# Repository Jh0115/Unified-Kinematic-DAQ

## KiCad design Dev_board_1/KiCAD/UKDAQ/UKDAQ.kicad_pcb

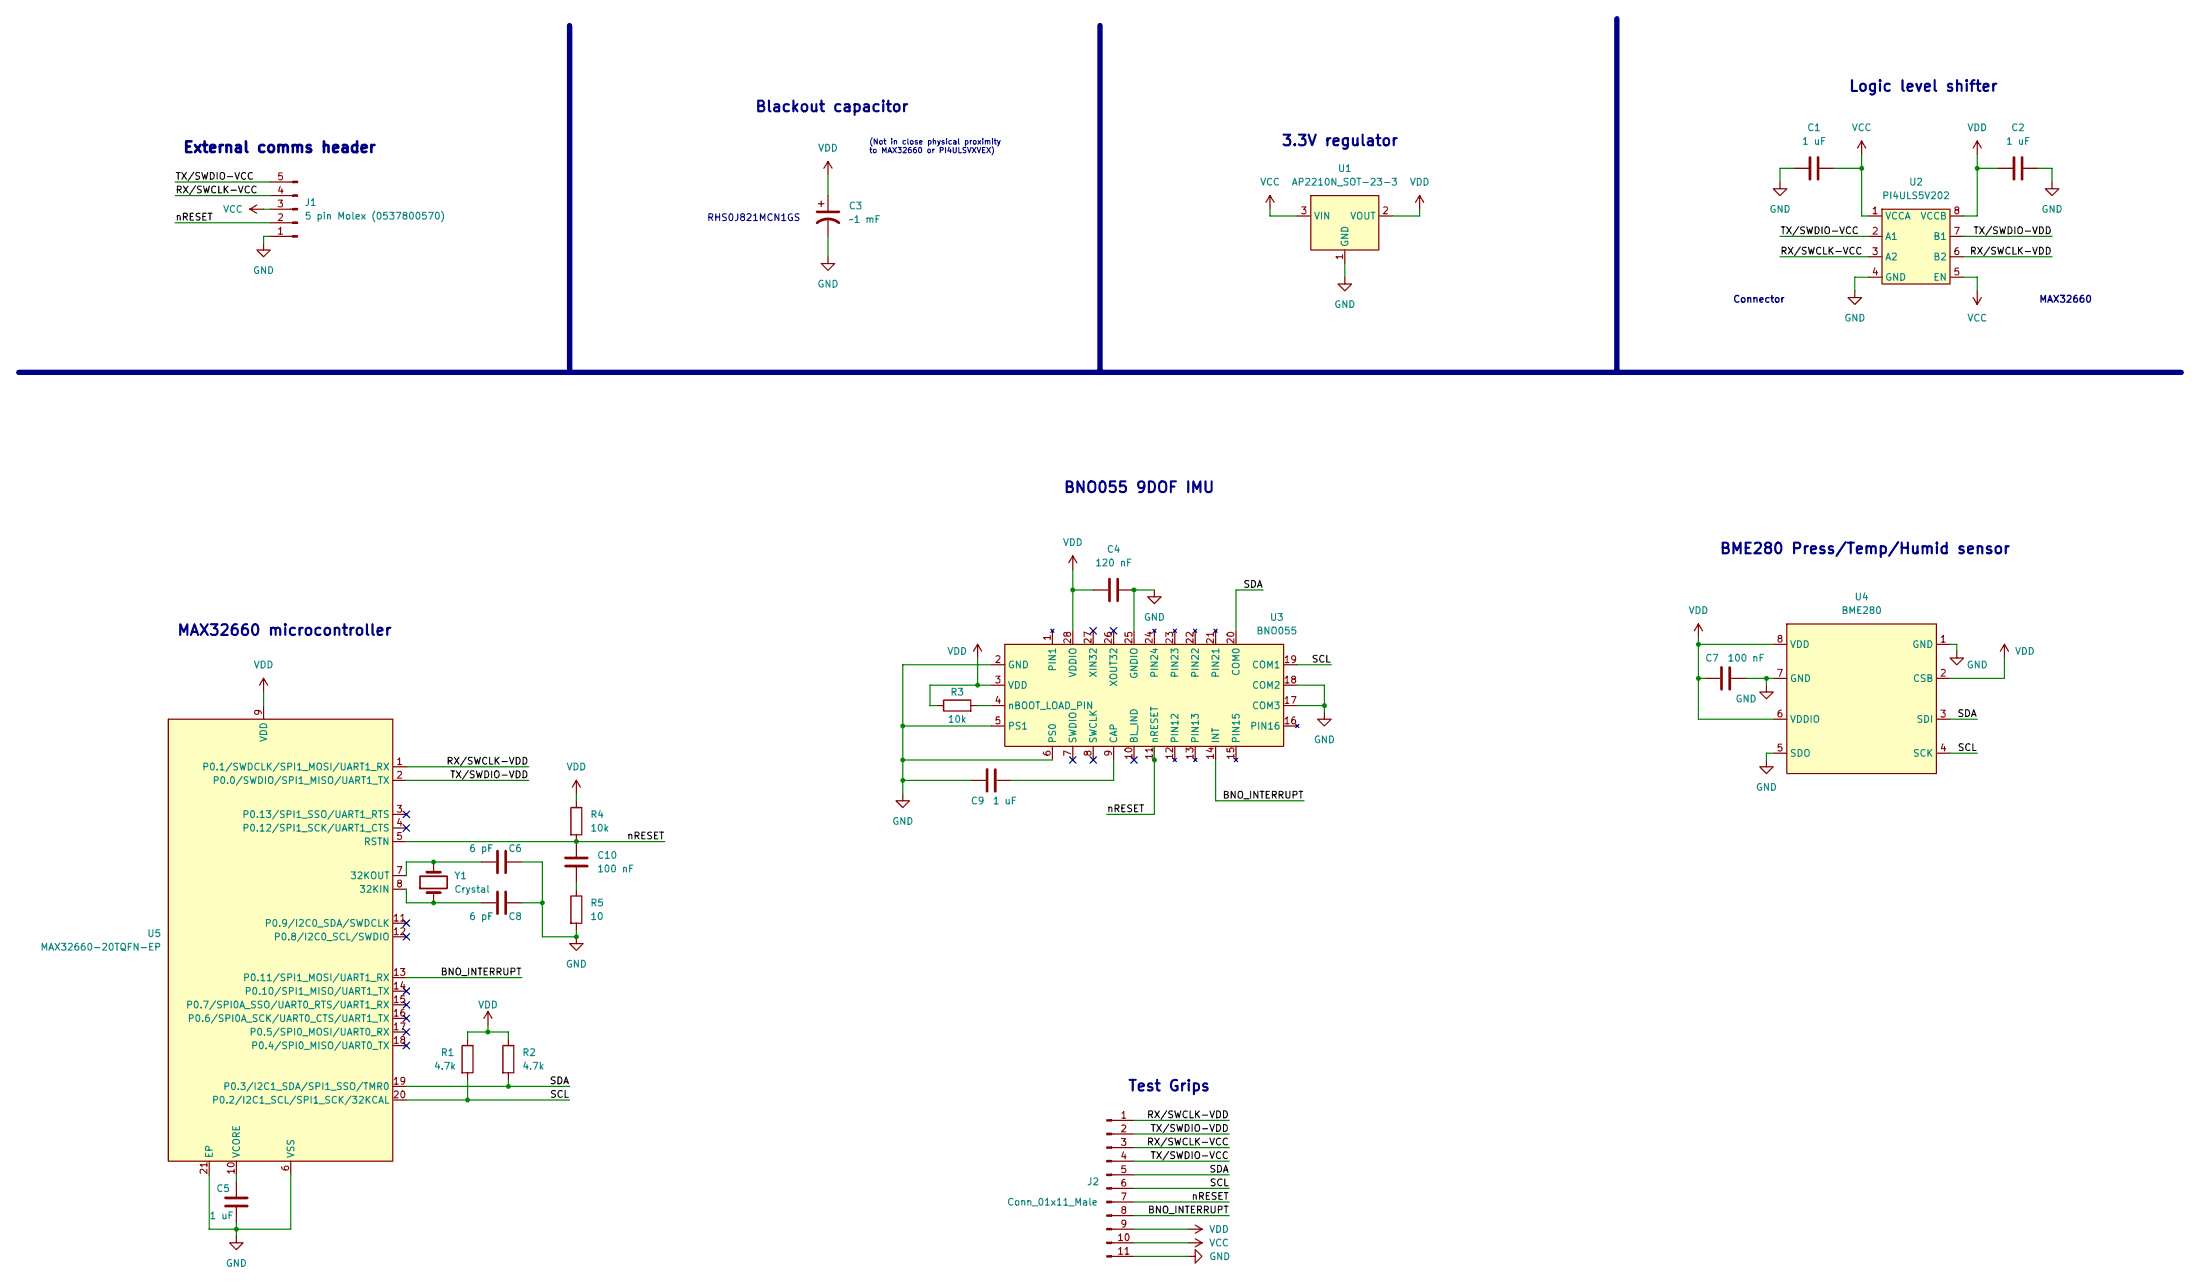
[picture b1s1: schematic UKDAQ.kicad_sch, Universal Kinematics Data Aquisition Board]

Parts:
C1, C2, C5, C9: 1 uF; C_0603_1608Metric
C3: ~1 mF; Can Capacitor - 493-3773-1-ND
C4: 120 nF; C_0603_1608Metric
C6, C8: 6 pF; C_0603_1608Metric
C7, C10: 100 nF; C_0603_1608Metric
J1: 5 pin Molex (0537800570); PinHeader_1x05_P2.54mm_Vertical
J2: Conn_01x11_Male; PinHeader_1x11_P2.54mm_Vertical
R1, R2: 4.7k; R_0402_1005Metric
R3, R4: 10k; R_0402_1005Metric
R5: 10; R_0402_1005Metric
U1: AP2210N_SOT-23-3; SOT-23
U2: PI4ULS5V202; MSOP-8
U3: BNO055; LGA28R50P4X10_380X520X100
U4: BME280
U5: MAX32660-20TQFN-EP; 21-0139V_T2044&plus_5_MXM
Y1: Crystal; Crystal_SMD_3215-2Pin_3.2x1.5mm

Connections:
/BNO_INTERRUPT: J2.8, U3.14 (INT), U5.13 (P0.11/SPI1_MOSI/UART1_RX)
/RX/SWCLK-VCC: J1.4, J2.3, U2.3 (A2)
/RX/SWCLK-VDD: J2.1, U2.6 (B2), U5.1 (P0.1/SWDCLK/SPI1_MOSI/UART1_RX)
/SCL: J2.6, R1.2, U3.19 (COM1), U4.4 (SCK), U5.20 (P0.2/I2C1_SCL/SPI1_SCK/32KCAL)
/SDA: J2.5, R2.2, U3.20 (COM0), U4.3 (SDI), U5.19 (P0.3/I2C1_SDA/SPI1_SSO/TMR0)
/TX/SWDIO-VCC: J1.5, J2.4, U2.2 (A1)
/TX/SWDIO-VDD: J2.2, U2.7 (B1), U5.2 (P0.0/SWDIO/SPI1_MISO/UART1_TX)
/nRESET: C10.1, J1.2, J2.7, R4.2, U3.11 (nRESET), U5.5 (RSTN)
GND: C1.1, C2.2, C3.2, C4.2, C5.2, C6.2, C7.2, C8.2, C9.1, J1.1, J2.11, R5.2, U1.1 (GND), U2.4 (GND), U3.2 (GND), U3.5 (PS1), U3.6 (PS0), U3.17 (COM3), U3.18 (COM2), U3.25 (GNDIO), U4.1 (GND), U4.5 (SDO), U4.7 (GND), U5.6 (VSS), U5.21 (EP)
unnamed: C5.1, U5.10 (VCORE)
unnamed: C6.1, U5.7 (32KOUT), Y1.2
unnamed: C8.1, U5.8 (32KIN), Y1.1
unnamed: C9.2, U3.9 (CAP)
unnamed: C10.2, R5.1
unnamed: R3.2, U3.4 (nBOOT_LOAD_PIN)
VCC: C1.2, J1.3, J2.10, U1.3 (VIN), U2.1 (VCCA), U2.5 (EN)
VDD: C2.1, C3.1, C4.1, C7.1, J2.9, R1.1, R2.1, R3.1, R4.1, U1.2 (VOUT), U2.8 (VCCB), U3.3 (VDD), U3.28 (VDDIO), U4.2 (CSB), U4.6 (VDDIO), U4.8 (VDD), U5.9 (VDD)

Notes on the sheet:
(Not in close physical proximity to MAX32660 or PI4ULSVXVEX)
MAX32660
Connector
BME280 Press/Temp/Humid sensor
External comms header
MAX32660 microcontroller
RHS0J821MCN1GS
Logic level shifter
3.3V regulator
Test Grips
Blackout capacitor
BNO055 9DOF IMU

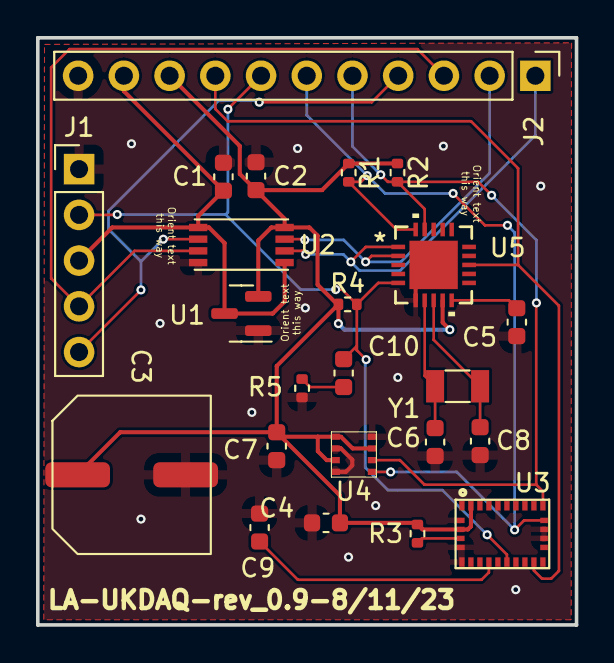
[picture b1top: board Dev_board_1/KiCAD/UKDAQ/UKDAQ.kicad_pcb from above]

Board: 2 copper layers, 29.9 x 32.6 mm, 23 parts (0 on the bottom side), 17 nets.

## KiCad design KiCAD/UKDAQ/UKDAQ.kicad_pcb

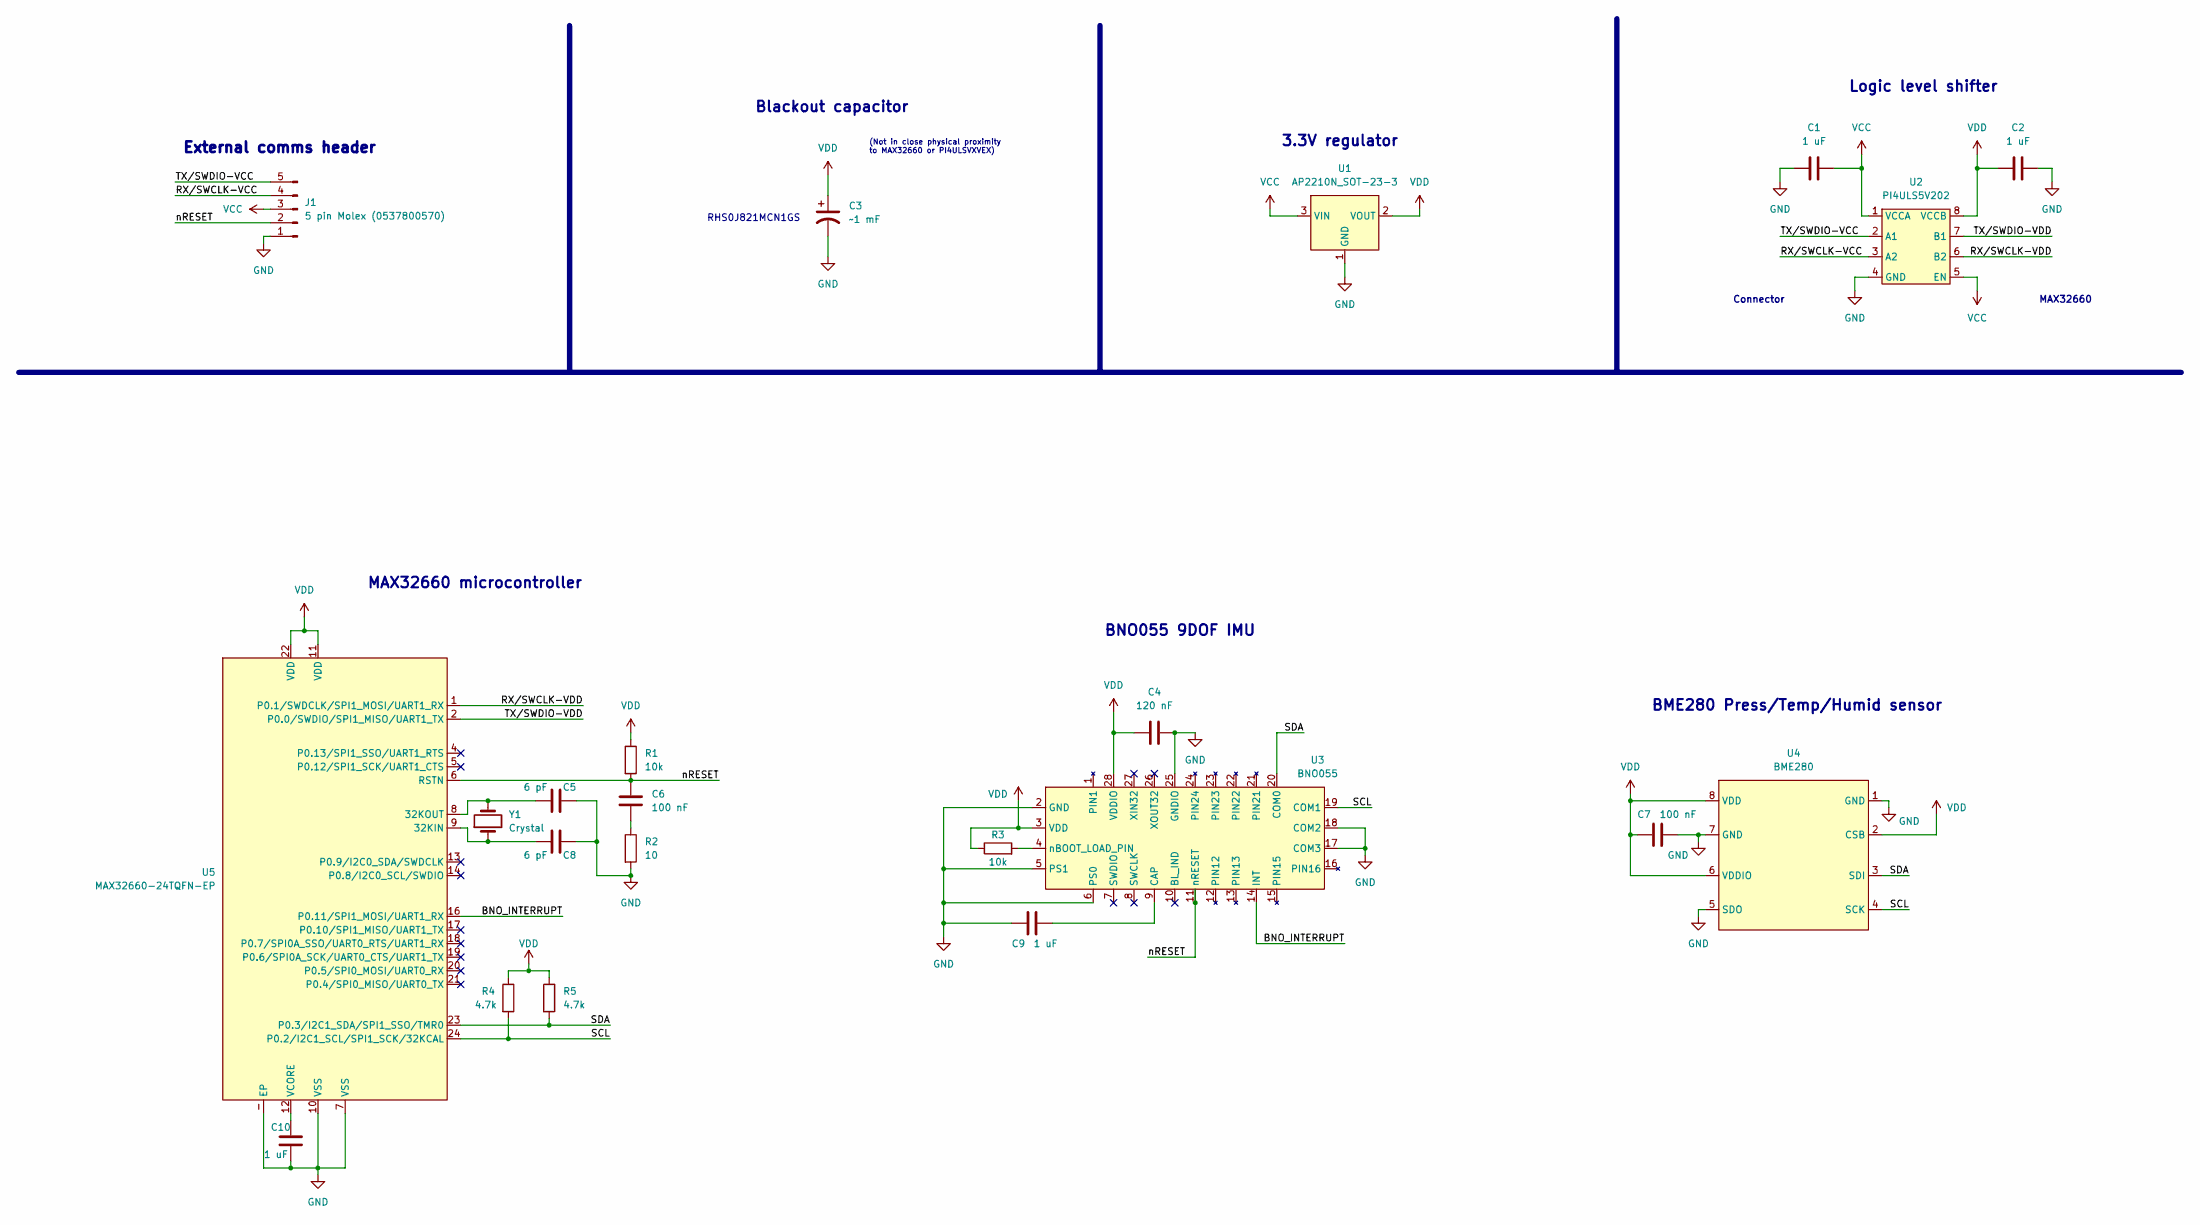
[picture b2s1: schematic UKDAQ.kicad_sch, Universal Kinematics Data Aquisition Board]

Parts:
C1, C2, C9, C10: 1 uF; C_0201_0603Metric
C3: ~1 mF; Can Capacitor - 493-3773-1-ND
C4: 120 nF; C_0603_1608Metric
C5, C8: 6 pF; C_01005_0402Metric
C6, C7: 100 nF; C_0603_1608Metric
J1: 5 pin Molex (0537800570); PinHeader_1x05_P2.54mm_Vertical
R1, R3: 10k; R_0402_1005Metric
R2: 10; R_0201_0603Metric
R4, R5: 4.7k; R_0402_1005Metric
U1: AP2210N_SOT-23-3; SOT-23
U2: PI4ULS5V202; OnSemi_UDFN-8_1.2x1.8mm_P0.4mm
U3: BNO055; LGA28R50P4X10_380X520X100
U4: BME280
U5: MAX32660-24TQFN-EP; MAX32660-24-TQFN-EP
Y1: Crystal; Crystal_SMD_3215-2Pin_3.2x1.5mm

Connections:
/BNO_INTERRUPT: U3.14 (INT), U5.16 (P0.11/SPI1_MOSI/UART1_RX)
/RX/SWCLK-VCC: J1.4, U2.3 (A2)
/RX/SWCLK-VDD: U2.6 (B2), U5.1 (P0.1/SWDCLK/SPI1_MOSI/UART1_RX)
/SCL: R4.2, U3.19 (COM1), U4.4 (SCK), U5.24 (P0.2/I2C1_SCL/SPI1_SCK/32KCAL)
/SDA: R5.2, U3.20 (COM0), U4.3 (SDI), U5.23 (P0.3/I2C1_SDA/SPI1_SSO/TMR0)
/TX/SWDIO-VCC: J1.5, U2.2 (A1)
/TX/SWDIO-VDD: U2.7 (B1), U5.2 (P0.0/SWDIO/SPI1_MISO/UART1_TX)
/nRESET: C6.1, J1.2, R1.2, U3.11 (nRESET), U5.6 (RSTN)
GND: C1.1, C2.2, C3.2, C4.2, C5.2, C7.2, C8.2, C9.1, C10.2, J1.1, R2.2, U1.1 (GND), U2.4 (GND), U3.2 (GND), U3.5 (PS1), U3.6 (PS0), U3.17 (COM3), U3.18 (COM2), U3.25 (GNDIO), U4.1 (GND), U4.5 (SDO), U4.7 (GND), U5.7 (VSS), U5.10 (VSS), U5.- (EP)
unnamed: C5.1, U5.8 (32KOUT), Y1.2
unnamed: C6.2, R2.1
unnamed: C8.1, U5.9 (32KIN), Y1.1
unnamed: C9.2, U3.9 (CAP)
unnamed: C10.1, U5.12 (VCORE)
unnamed: R3.2, U3.4 (nBOOT_LOAD_PIN)
VCC: C1.2, J1.3, U1.3 (VIN), U2.1 (VCCA), U2.5 (EN)
VDD: C2.1, C3.1, C4.1, C7.1, R1.1, R3.1, R4.1, R5.1, U1.2 (VOUT), U2.8 (VCCB), U3.3 (VDD), U3.28 (VDDIO), U4.2 (CSB), U4.6 (VDDIO), U4.8 (VDD), U5.11 (VDD), U5.22 (VDD)

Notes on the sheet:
(Not in close physical proximity to MAX32660 or PI4ULSVXVEX)
MAX32660
Connector
BME280 Press/Temp/Humid sensor
External comms header
MAX32660 microcontroller
RHS0J821MCN1GS
Logic level shifter
3.3V regulator
Blackout capacitor
BNO055 9DOF IMU

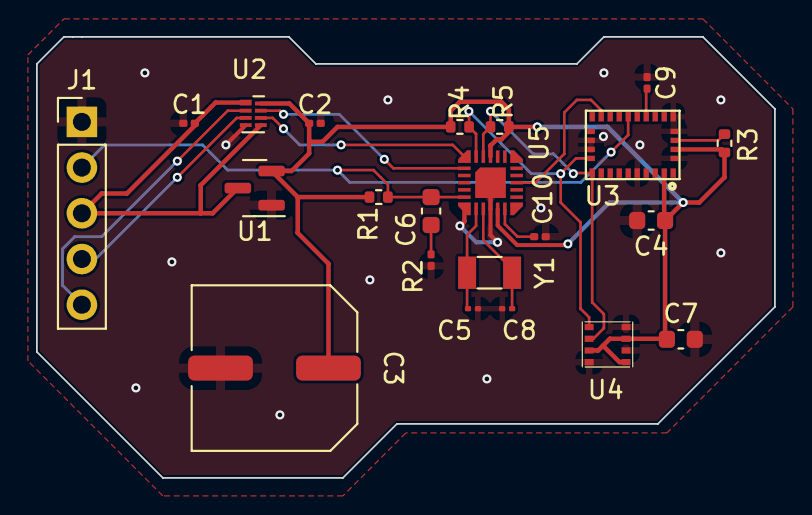
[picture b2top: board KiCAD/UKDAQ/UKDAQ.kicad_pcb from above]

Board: 2 copper layers, 41.0 x 24.5 mm, 22 parts (0 on the bottom side), 17 nets.

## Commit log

2022-10-10 initial commit, created kicad file for primary board
2022-10-13 Added dev-board code
2022-10-13 more additions to the dev board files
2022-10-19 added important documents folder
2022-10-19 added documents
2022-10-20 created eclipse IDE workspace for dev kit
2022-10-21 data visualization tool
2022-10-21 data visualization tool with quaternion reference frame correction
2022-10-23 First test jumps Mitchell low pull HnP
2022-10-24 Not sure what changed
2022-12-03 Lots of changes since learning how to program max32660
2022-12-04 many schematic updates, rev 1 started
2022-12-04 5 pin header for reset pin instead of 4
2022-12-04 some more updates before bedtime
2022-12-04 added bme280, swapped back to i2c because bno doesnt support spi, and finished max32660 subschematic
2022-12-04 First version of schematic done! about to do design rule checks!
2022-12-04 made some corrections via the design rule checker. Some complaints about power pins but itll probably be fine.
2022-12-05 finalized schematic and worked on specific BOM
2022-12-07 untangled the rats nest in PCB editor
2022-12-07 routed traces (LAZY AS FUCK) gonna do ground pour and ground pads tommorow
2022-12-08 PCB done yippe probably gonna haftaredo la8r
2022-12-09 added up costs and ordered first dev board parts
2023-01-01 oops i forgot to push this for a while
2023-02-24 updated dev board 1 to rev 2 design
2023-02-24 bleh
2023-04-27 small change to MCU footprint
2023-06-23 changes to board design and new BOM
2023-07-13 Used triangles on MCU paste stencil pads
2023-08-10 Havent pushed in a while. Dev board is now baseline functional
2023-08-12 Shrunk size of the dev board significantly
2023-09-05 printed a strain relief device for the programmer wires
2023-09-05 Began software requirements investigation
2024-01-05 centrifuge motor control using ramping velocity
2024-01-06 motor controller can now decellerate please ignore all the runSpeed() functions and dont ask me about it unless you want anger.
2024-04-19 Routine push
2024-04-28 Finally got esp32 to transmit data consistently
